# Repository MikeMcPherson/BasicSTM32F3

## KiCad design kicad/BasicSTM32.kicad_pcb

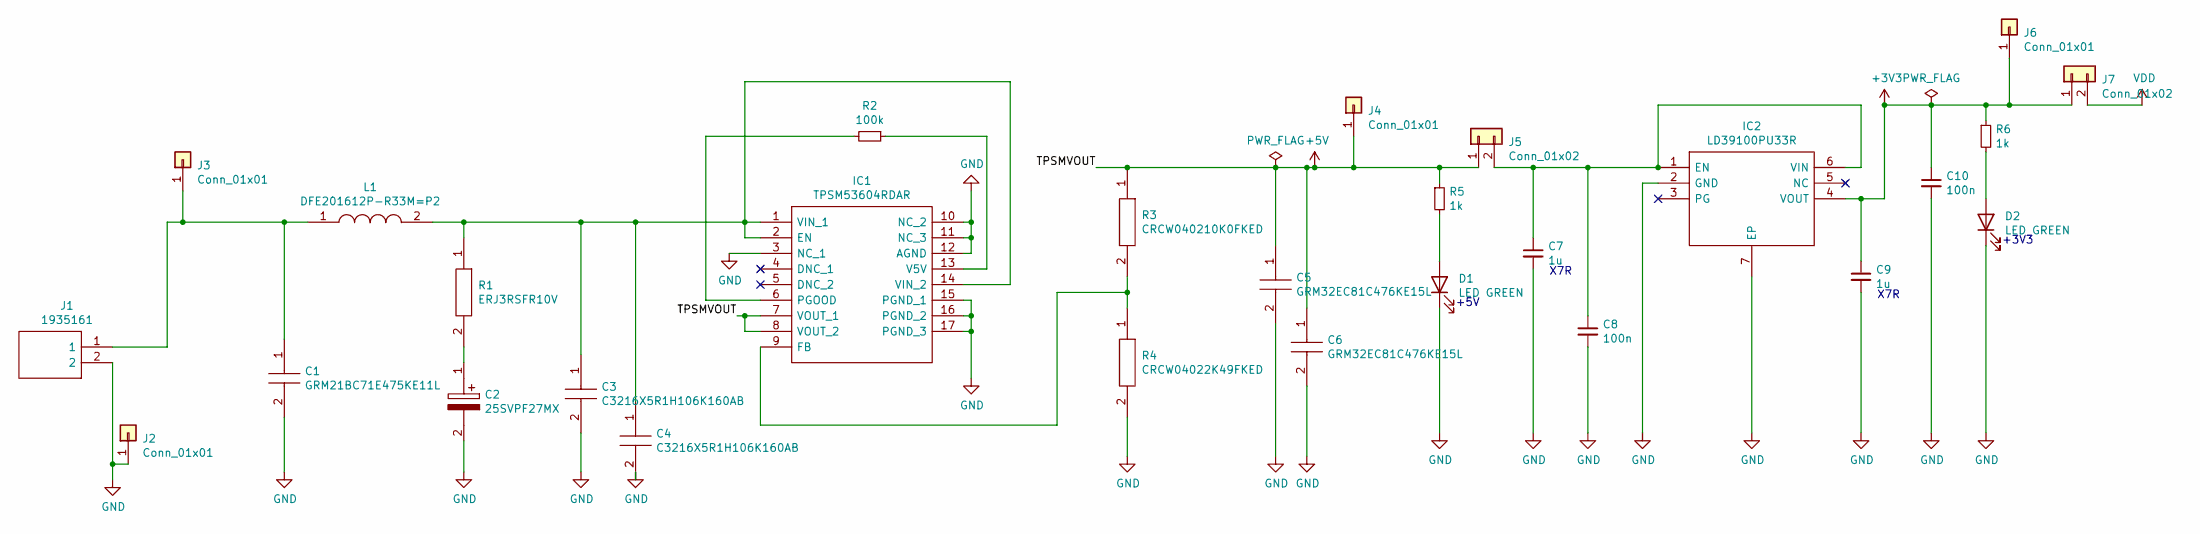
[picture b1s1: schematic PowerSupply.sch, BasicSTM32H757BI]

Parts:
C1: GRM21BC71E475KE11L; CAPC2012X145N; Manufacturer_Part_Number GRM21BC71E475KE11L; Mouser Part Number 81-GRM21BC71E475KE1L
C2: 25SVPF27MX; CAPAE530X600N; Manufacturer_Part_Number 25SVPF27MX; Mouser Part Number 667-25SVPF27MX
C3, C4: C3216X5R1H106K160AB; CAPC3216X180N; Manufacturer_Part_Number C3216X5R1H106K160AB; Mouser Part Number 810-C3216X5R1H106K
C5, C6: GRM32EC81C476KE15L; CAPC3225X270N; Manufacturer_Part_Number GRM32EC81C476KE15L; Mouser Part Number 81-GRM32EC81C476KE5L
C7, C9: 1u; C_0603_1608Metric
C8, C10: 100n; C_0603_1608Metric
D1, D2: LED GREEN; LED_0603_1608Metric
IC1: TPSM53604RDAR; Manufacturer_Part_Number TPSM53604RDAR; Mouser Part Number 595-TPSM53604RDAR
IC2: LD39100PU33R; SON95P300X300X100-7N-D; Manufacturer_Part_Number LD39100PU33R; Mouser Part Number 511-LD39100PU33R
J1: 1935161; 1701023; Manufacturer_Part_Number 1935161; Mouser Part Number 651-1935161
J2, J3, J4, J6: Conn_01x01; PinHeader_1x01_P2.54mm_Vertical
J5, J7: Conn_01x02; PinHeader_1x02_P2.54mm_Vertical
L1: DFE201612P-R33M=P2; 1286ASH1R0MP2; Manufacturer_Part_Number DFE201612P-R33M=P2; Mouser Part Number 81-DFE201612P-R33MP2
R1: ERJ3RSFR10V; RESC1608X55N; Manufacturer_Part_Number ERJ3RSFR10V
R2: 100k; R_0603_1608Metric
R3: CRCW040210K0FKED; RESC1005X40N; Manufacturer_Part_Number CRCW040210K0FKED; Mouser Part Number 71-CRCW0402-10K-E3
R4: CRCW04022K49FKED; RESC1005X40N; Manufacturer_Part_Number CRCW04022K49FKED; Mouser Part Number 71-CRCW0402-2.49K-E3
R5, R6: 1k; R_0603_1608Metric

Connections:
+3V3: C9.1, C10.1, IC2.4 (VOUT), J6.1, J7.1, R6.1
+5V: C5.1, C6.1, IC1.7 (VOUT_1), IC1.8 (VOUT_2), J4.1, J5.1, R3.1, R5.1; also elsewhere on the board
GND: C1.2, C2.2, C3.2, C4.2, C5.2, C6.2, C7.2, C8.2, C9.2, C10.2, D1.1 (K), D2.1 (K), IC1.3 (NC_1), IC1.10 (NC_2), IC1.11 (NC_3), IC1.12 (AGND), IC1.15 (PGND_1), IC1.16 (PGND_2), IC1.17 (PGND_3), IC2.2 (GND), IC2.7 (EP), J1.2, J2.1, R4.2; also elsewhere on the board
unnamed: C1.1, J1.1, J3.1, L1.1
unnamed: C2.1, R1.2
unnamed: C3.1, C4.1, IC1.1 (VIN_1), IC1.2 (EN), IC1.14 (VIN_2), L1.2, R1.1
unnamed: C7.1, C8.1, IC2.1 (EN), IC2.6 (VIN), J5.2
unnamed: D1.2 (A), R5.2
unnamed: D2.2 (A), R6.2
unnamed: IC1.6 (PGOOD), R2.2
unnamed: IC1.9 (FB), R3.2, R4.1
unnamed: IC1.13 (V5V), R2.1
VDD: J7.2; also elsewhere on the board

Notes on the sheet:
X7R
+5V
+3V3

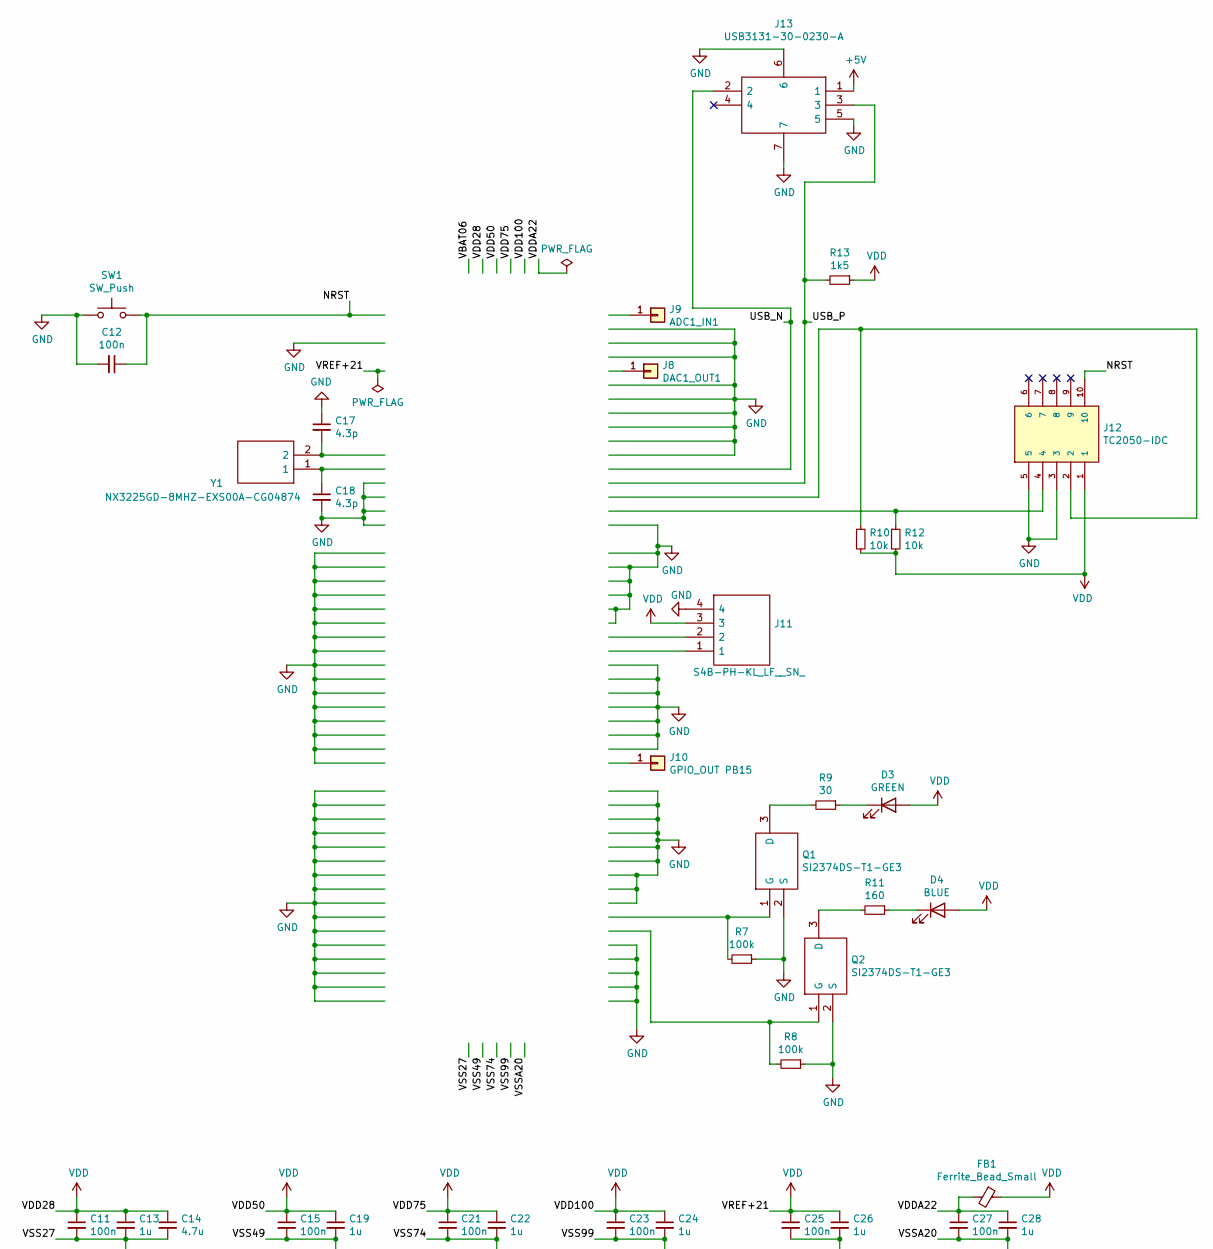
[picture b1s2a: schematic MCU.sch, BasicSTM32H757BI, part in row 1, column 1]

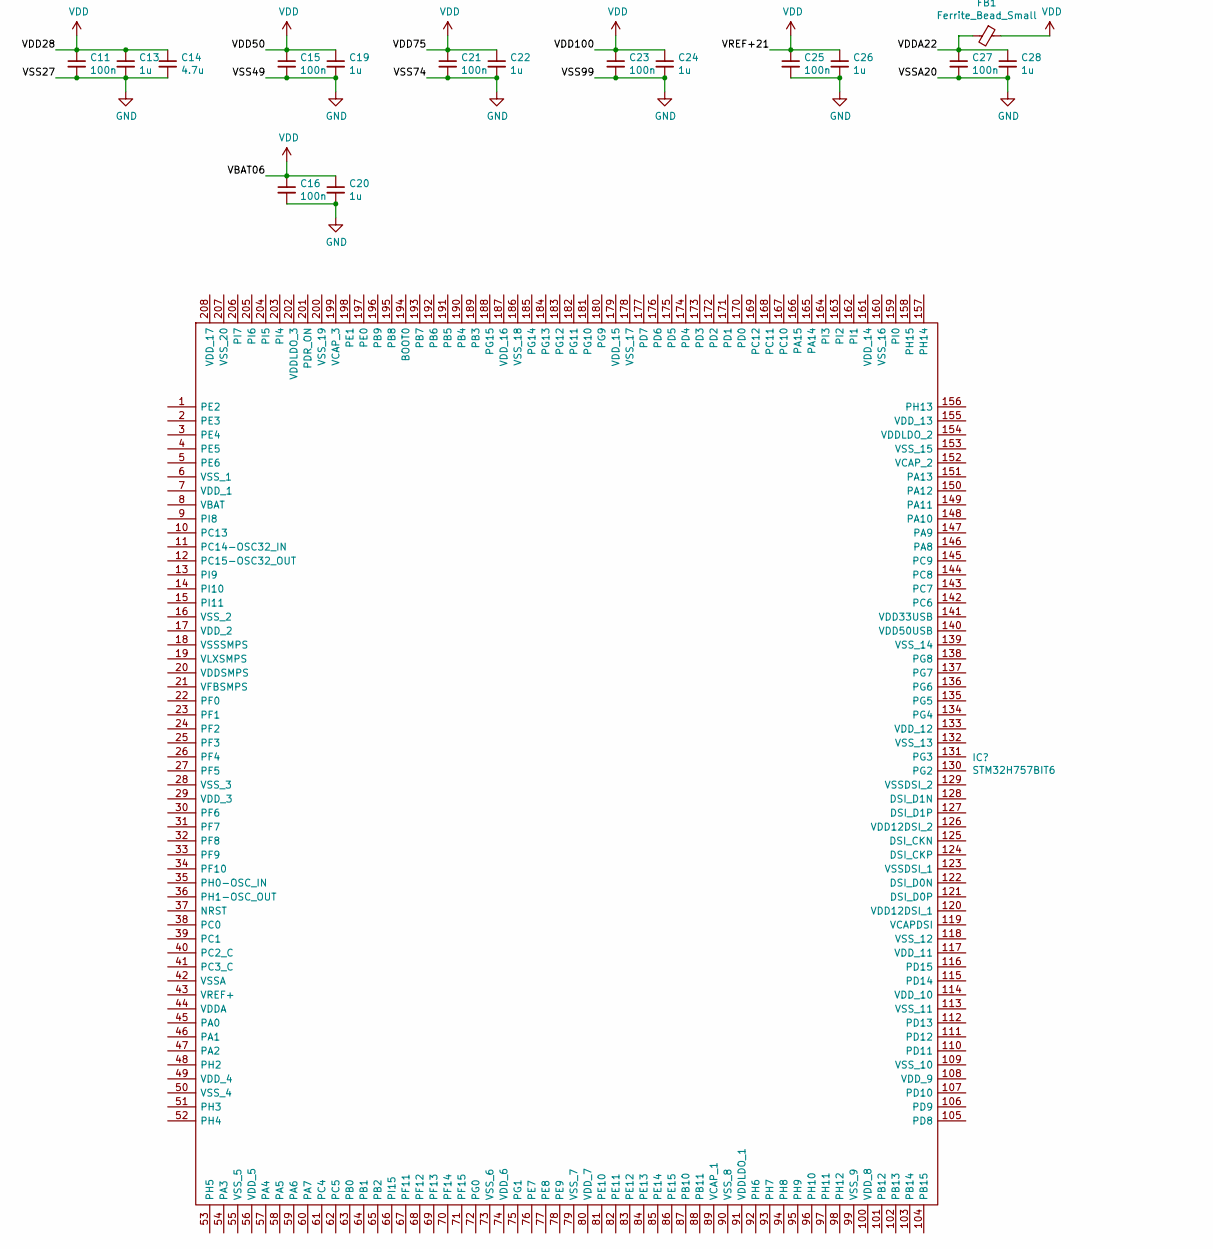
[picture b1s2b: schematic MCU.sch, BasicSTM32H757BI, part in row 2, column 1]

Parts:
C11, C12, C15, C16, C21, C23, C25, C27: 100n; C_0603_1608Metric
C13, C19, C20, C22, C24, C26, C28: 1u; C_0603_1608Metric
C14: 4.7u; C_0603_1608Metric
C17, C18: 4.3p; C_0603_1608Metric
D3: GREEN; LED_0603_1608Metric
D4: BLUE; LED_0603_1608Metric
FB1: Ferrite_Bead_Small; LairdTech_28C0236-0JW-10
J8: DAC1_OUT1; PinHeader_1x01_P2.54mm_Vertical
J9: ADC1_IN1; PinHeader_1x01_P2.54mm_Vertical
J10: GPIO_OUT PB15; PinHeader_1x01_P2.54mm_Vertical
J11: S4B-PH-KL_LF__SN_; S4BPHKLLFSN; Manufacturer_Part_Number S4B-PH-KL(LF)(SN)
J12: TC2050-IDC; TAG-CONNECT_TC2050-IDC; PARTREV A
J13: USB3131-30-0230-A; USB3131300230A; Manufacturer_Part_Number USB3131-30-0230-A; Mouser Part Number 640-USB3131300230A
Q1, Q2: SI2374DS-T1-GE3; SOT95P237X112-3N; Manufacturer_Part_Number SI2374DS-T1-GE3; Mouser Part Number 78-SI2374DS-T1-GE3
R7, R8: 100k; R_0603_1608Metric
R9: 30; R_0603_1608Metric
R10, R12: 10k; R_0603_1608Metric
R11: 160; R_0603_1608Metric
R13: 1k5; R_0603_1608Metric
SW1: SW_Push; SW_Push_1P1T_NO_Vertical_Wuerth_434133025816
Y1: NX3225GD-8MHZ-EXS00A-CG04874; NX3225SA25000MSTDCSR6; Manufacturer_Part_Number NX3225GD-8MHZ-EXS00A-CG04874

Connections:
+5V: J13.1; also elsewhere on the board
/MCU/NRST: C12.1, J12.10, SW1.2; also elsewhere on the board
/MCU/USB_N: J13.2; also elsewhere on the board
/MCU/USB_P: J13.3, R13.2; also elsewhere on the board
/MCU/VDDA22: C27.1, C28.1, FB1.2; also elsewhere on the board
GND: C11.2, C12.2, C13.2, C14.2, C15.2, C16.2, C17.1, C18.2, C19.2, C20.2, C21.2, C22.2, C23.2, C24.2, C25.2, C26.2, C27.2, C28.2, J11.4, J12.3, J12.5, J13.5, J13.6, J13.7, Q1.2 (S), Q2.2 (S), R7.1, R8.1, SW1.1; also elsewhere on the board
unnamed 11: C17.2, Y1.2; also elsewhere on the board
unnamed 12: C18.1, Y1.1; also elsewhere on the board
unnamed: D3.1 (K), R9.1
unnamed: D4.1 (K), R11.1
unnamed 20: J8.1; also elsewhere on the board
unnamed 21: J9.1; also elsewhere on the board
unnamed 22: J10.1; also elsewhere on the board
unnamed 23: J11.1; also elsewhere on the board
unnamed 24: J11.2; also elsewhere on the board
unnamed 25: J12.2, R10.1; also elsewhere on the board
unnamed 26: J12.4, R12.1; also elsewhere on the board
unnamed 27: Q1.1 (G), R7.2; also elsewhere on the board
unnamed: Q1.3 (D), R9.2
unnamed 29: Q2.1 (G), R8.2; also elsewhere on the board
unnamed: Q2.3 (D), R11.2
VDD: C11.1, C13.1, C14.1, C15.1, C16.1, C19.1, C20.1, C21.1, C22.1, C23.1, C24.1, C25.1, C26.1, D3.2 (A), D4.2 (A), FB1.1, J11.3, J12.1, R10.2, R12.2, R13.1; also elsewhere on the board

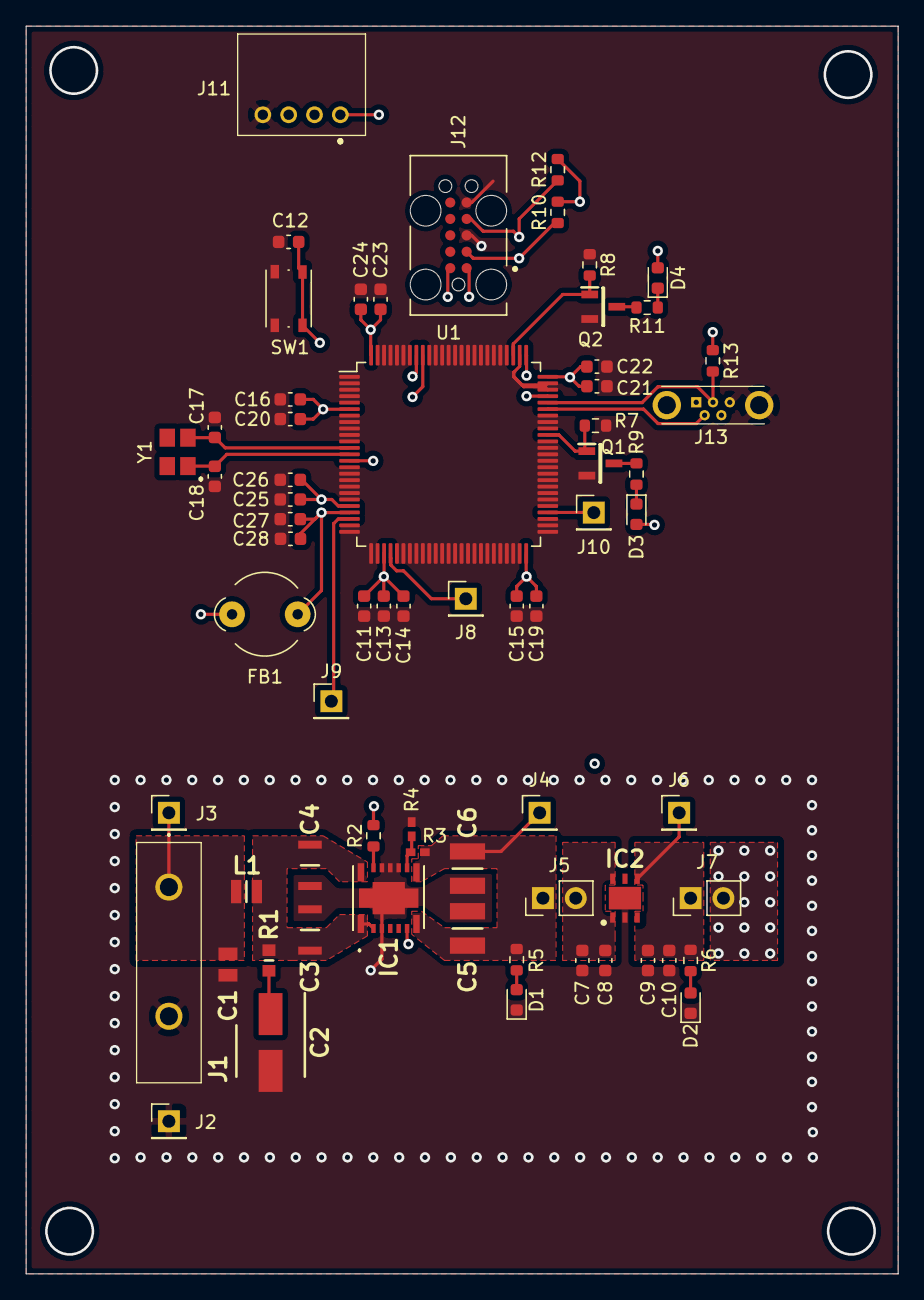
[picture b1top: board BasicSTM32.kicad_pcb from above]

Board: 4 copper layers, 67.5 x 96.6 mm, 67 parts (0 on the bottom side), 32 nets.

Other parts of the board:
U1: STM32F303VETx; LQFP-100_14x14mm_P0.5mm

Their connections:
/MCU/NRST: U1.14; also elsewhere on the board
/MCU/USB_N: U1.70; also elsewhere on the board
/MCU/USB_P: U1.71; also elsewhere on the board
/MCU/VDDA22: U1.22; also elsewhere on the board
GND: U1.1, U1.2, U1.3, U1.4, U1.5, U1.7, U1.8, U1.9, U1.10, U1.11, U1.15, U1.16, U1.17, U1.18, U1.19, U1.20, U1.24, U1.25, U1.26, U1.27, U1.30, U1.31, U1.32, U1.33, U1.34, U1.35, U1.36, U1.37, U1.38, U1.39, U1.40, U1.41, U1.42, U1.43, U1.44, U1.45, U1.46, U1.47, U1.48, U1.49, U1.51, U1.52, U1.53, U1.55, U1.56, U1.57, U1.58, U1.59, U1.60, U1.61, U1.62, U1.63, U1.64, U1.65, U1.67, U1.68, U1.69, U1.73, U1.74, U1.77, U1.79, U1.80, U1.81, U1.82, U1.83, U1.84, U1.85, U1.86, U1.87, U1.88, U1.89, U1.90, U1.91, U1.94, U1.95, U1.96, U1.97, U1.98, U1.99; also elsewhere on the board
unnamed 11: U1.12; also elsewhere on the board
unnamed 12: U1.13; also elsewhere on the board
unnamed 20: U1.29; also elsewhere on the board
unnamed 21: U1.23; also elsewhere on the board
unnamed 22: U1.54; also elsewhere on the board
unnamed 23: U1.93; also elsewhere on the board
unnamed 24: U1.92; also elsewhere on the board
unnamed 25: U1.72; also elsewhere on the board
unnamed 26: U1.76; also elsewhere on the board
unnamed 27: U1.66; also elsewhere on the board
unnamed 29: U1.78; also elsewhere on the board
VDD: U1.6, U1.21, U1.28, U1.50, U1.75, U1.100; also elsewhere on the board

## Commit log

2021-03-26 Power supply layout
2021-03-29 Start MCU layout
2021-03-29 Continue MCU layout
2021-03-30 Finish layout first pass
2021-05-14 Add USB
2021-05-18 Finish PCB layout and routing
2021-09-09 Move docs to central collection; fine-tune schematic
2021-09-09 Place basic power; place osc, boot, nrst
2021-09-10 Complete power and ground
